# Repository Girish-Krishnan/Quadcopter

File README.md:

# Quadcopter

*Made by Girish Krishnan and Anish Kulkarni*

---

Hardware and firmware for a compact 4‑rotor UAV.
[**Watch the demo videos on YouTube!**](https://www.youtube.com/playlist?list=PLE_L-WPduPxbYMuvPQKa1v5fUpK1VIxrP)

|| |
|---|---|

This project contains hardware and firmware for a custom 4‑rotor UAV. The design is based on the ATmega128RFA1 microcontroller which integrates a 2.4 GHz radio. The repository includes the printed circuit board layout, flight controller firmware, and code for a handheld remote.

**Note**: The specific code files and CAD files are currently private, but you can contact me for more details.

## Table of Contents
- [Quadcopter](#quadcopter)
  - [Table of Contents](#table-of-contents)
  - [Features](#features)
  - [System Overview](#system-overview)
  - [Hardware Overview](#hardware-overview)
  - [Firmware Overview](#firmware-overview)
    - [Wireless Protocol](#wireless-protocol)
    - [Flight Controller](#flight-controller)
    - [Remote Firmware](#remote-firmware)
    - [PID Control Loops](#pid-control-loops)
    - [State Machines](#state-machines)
      - [Quadcopter](#quadcopter-1)
      - [Remote](#remote)
  - [Building and Uploading](#building-and-uploading)

## Features
- Flight controller based on the ATmega128RFA1 with integrated 2.4 GHz radio
- Handheld remote with dual gimbals, LCD and menu navigation
- Telemetry link for battery monitoring and state feedback
- PID tuning directly from the remote
- Four-layer PCB with on-board ESC drivers and IMU

## System Overview

The project consists of two main pieces of hardware:

1. **Quadcopter** – a compact flight controller board driving four brushless motors via electronic speed controllers (ESCs).
2. **Remote** – a handheld transmitter with gimbal sticks, buttons and an LCD that sends pilot commands over 2.4 GHz.

The diagram below summarizes the high–level flow of data and control.

```mermaid
graph LR
    Remote[(Handheld Remote)] -- 2.4GHz --> MCU[ATmega128RFA1]
    MCU --> IMU[LSM6DSOX IMU]
    MCU --> ESCs
    ESCs --> Motors
    MCU -- Telemetry --> Remote
```

## Hardware Overview

The quadcopter PCB is a four‑layer board measuring 119×119 mm with red soldermask and white silkscreen. Major components:

- **ATmega128RFA1** MCU with onboard 2.4 GHz transceiver
- **LSM6DSOX** IMU for 3‑axis gyro and accelerometer
- FET motor drivers for four brushless ESCs
- Power regulation, battery monitor (via `BAT_SENSE_PIN`), and status LEDs
- Connectors for an external receiver and programming headers

Here is a schematic overview of the quadcopter:

Here is the layout of the quadcopter PCB, showing the placement of components and routing:

Here are pictures of the top and bottom layers of the PCB:

|||
|---|---|
| Top Layer | Bottom Layer |

## Firmware Overview

### Wireless Protocol

The on-board radio communicates with the remote using packets. Packets carry user commands, PID gains, trims, and telemetry such as battery level.

### Flight Controller

The flight controller reads the LSM6DSOX IMU using the Adafruit AHRS library. A complementary filter and PID loop produce motor outputs:

- Desired roll/pitch/yaw are received from the remote.
- IMU data is converted to angles and rates.
- Proportional, integral and derivative terms are computed every loop.
- Four PWM outputs drive the motors which mixes PID outputs to each rotor.

State transitions are received wirelessly. The code also reports back battery percentage every second.

### Remote Firmware

The remote uses analog gimbals, push buttons, a rotary encoder and a SerLCD display. It calibrates the joystick range to map raw ADC values to 0–255 and stores them in EEPROM. In the armed state, pressing the encoder or buttons adjusts trim values which are sent in each packet.

Incoming packets from the quad provide its state and battery status so the remote can display feedback to the user.

The remote hardware exposes the following controls:

- Two gimbal sticks (yaw/throttle and roll/pitch) wired to analog inputs A0–A3.
- A rotary encoder with push‑button for menu navigation.
- Five directional buttons for trims and menu actions.
- A small serial LCD showing mode and battery levels.

### PID Control Loops

Here is the setup used for tuning the PID for the roll and pitch axes:

The flight controller stabilizes the aircraft using three independent PID loops
for roll, pitch and yaw. Error values are computed from the difference between
the desired setpoint (received from the remote) and the measured angle or rate
from the IMU. Each loop produces a correction that is mixed into the individual
motor commands.

```mermaid
graph TD
    R[Remote input] -->|setpoint| E[Error]
    IMU -- feedback --> E
    E --> P[P gain]
    E --> I[I gain]
    E --> D[D gain]
    P --> SUM
    I --> SUM
    D --> SUM
    SUM --> MIX(Motor Mixer)
    MIX --> Motors
```

### State Machines
#### Quadcopter

```mermaid
stateDiagram-v2
    direction LR
    [*] --> QUAD_RESET
    QUAD_RESET --> DISARMED: Startup complete
    DISARMED --> ARMED: Receive ARM
    ARMED --> DISARMED: Receive DISARM or link loss
```

#### Remote

```mermaid
stateDiagram-v2
    direction LR
    [*] --> DISARMED
    DISARMED --> CALIBRATION: Center button
    CALIBRATION --> DISARMED: Save calibration
    DISARMED --> ARMED: Stick combo 3s
    ARMED --> DISARMED: Center button or QUAD_RESET from quad
 ```

## Building and Uploading

Follow the instructions in [NVSL QuadClass Resources](https://github.com/NVSL/QuadClass-Resources/tree/master) to get started.

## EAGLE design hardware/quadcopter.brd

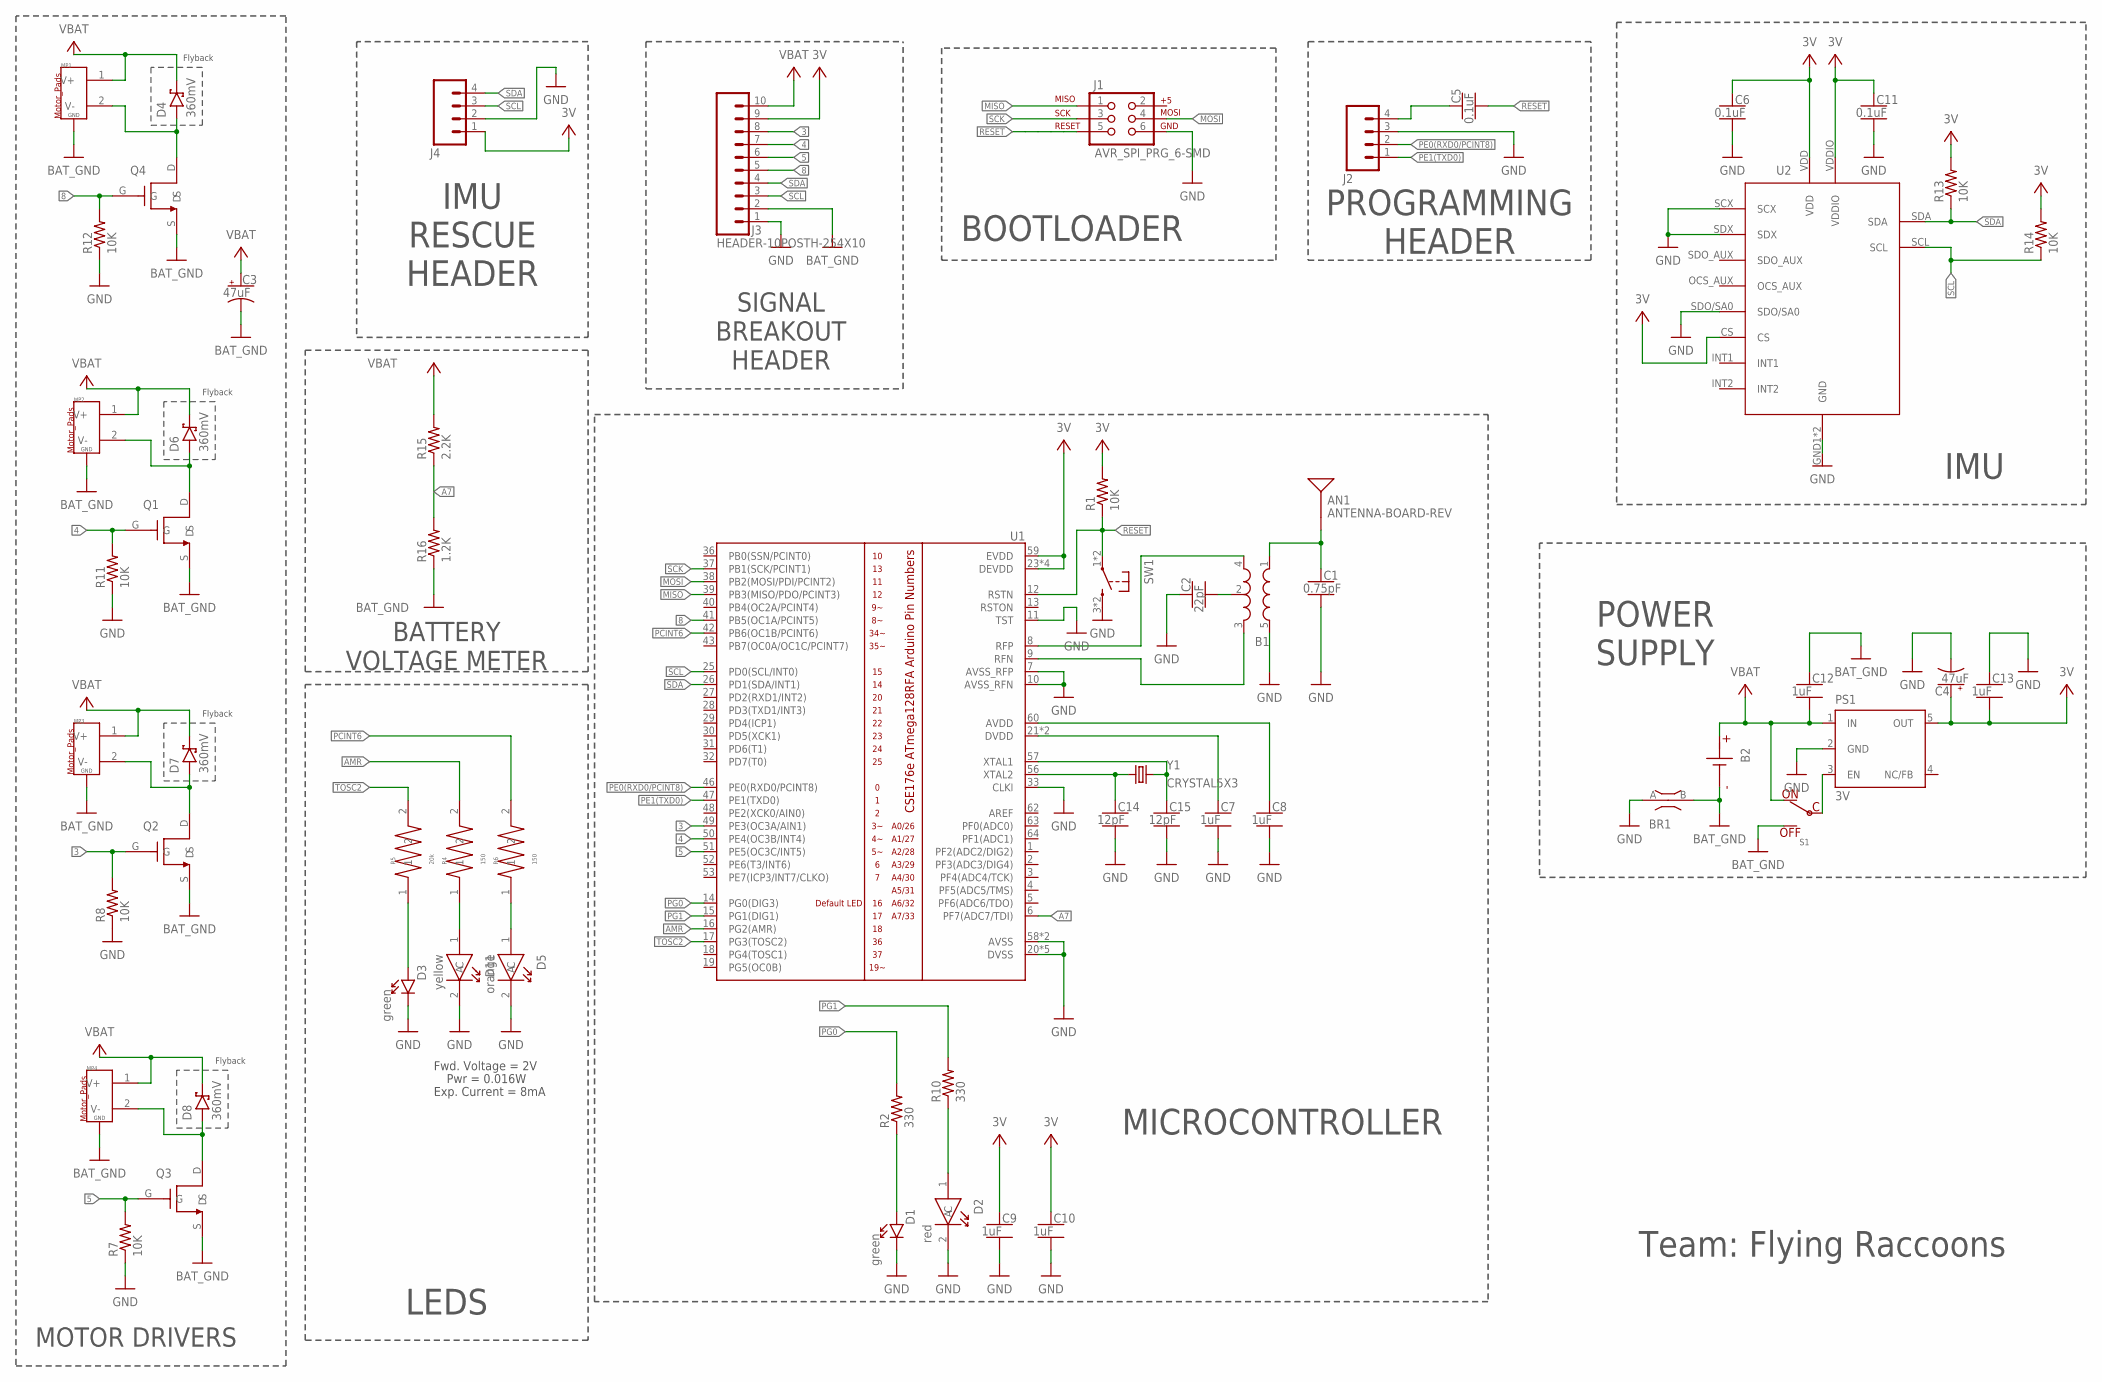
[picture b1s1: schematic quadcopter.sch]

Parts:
AN1: ANTENNA-BOARD-REV; ANT_PCB_2.4GHZ_NRF8001_1.6MM_1OZ_REV
B1: BALUN0805; BALUN
B2: BATTERY-SCREW-TERMINAL; SCREW-TERMINAL-1X2-2.54MM
BR1: NET_BRIDGE-NET-BRIDGE; BRIDGE
C1: 0.75pF; CAPC2012X140_HS
C2: 22pF; CAPC2012X140_HS
C3, C4: 47uF; CAPMP3216X180
C5, C6, C11: 0.1uF; CAPC2012X140_HS
C7, C8, C9, C10, C12, C13: 1uF; CAPC2012X140_HS
C14, C15: 12pF; CAPC2012X140_HS
D1, D3: green; LEDSC125X200X120-2_HS
D2: red; LED-LTST-C170EKT
D4, D6, D7, D8: 360mV; SODFL3516X96
D5: orange; LED-LTST-C170EKT
D11: yellow; LED-LTST-C170EKT
J1: AVR_SPI_PRG_6-SMD; 2X3-SMD
J2, J4: HEADER-4POS-0.1IN-FEMALE-SMD-BOTTOM-ENTRY; HEADER-1X4-BOTTOM-ENTRY
J3: HEADER-10POSTH-254X10; HDRV10W63P254_10X1_2540X254H838_HS
MP1, MP2, MP3, MP4: MOTOR_PADS_GND-MOLEX-SMD; MOLEX-0532610271
PS1: 3V; SOT23-DBV
Q1, Q2, Q3, Q4: NMOSFET; SOTFL95P237X112-3N
R1, R7, R8, R11, R12, R13, R14: 10K; RESC2012X60_HS
R2, R10: 330; RESC2012X60_HS
R4, R6: 150; 0805_RESISTOR
R5: 20k; 0805_RESISTOR
R15: 2.2K; RESC2012X60_HS
R16: 1.2K; RESC2012X60_HS
S1: POWER-SWITCH-MFS201N-9-Z-SMD-EDGE; JS102011SAQN
SW1: PUSHBUTTON_-4.5X4.5; 4.5MM_TACTILE_SWITCH_TL3305AF160QG
U1: ATMEGA128RFA1; QFN-64
U2: IMU_LSM6DS0XTR-IMU-LSM6DS0XTR; IMU_LSM6DS0XTR
Y1: CRYSTAL5X3; CRYSTAL-SMD-5X3

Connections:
3: J3.8, Q2.G, R8.2, U1.49 (PE3(OC3A/AIN1))
3V: C4.1 (+), C6.1, C9.1, C10.1, C11.1, C13.2, J3.9, J4.1, PS1.5 (OUT), R1.2, R13.2, R14.2, U1.23 (DEVDD), U1.34 (DEVDD), U1.44 (DEVDD), U1.54 (DEVDD), U1.59 (EVDD), U2.CS, U2.VDD, U2.VDDIO
4: J3.7, Q1.G, R11.2, U1.50 (PE4(OC3B/INT4))
5: J3.6, Q3.G, R7.2, U1.51 (PE5(OC3C/INT5))
8: J3.5, Q4.G, R12.2, U1.41 (PB5(OC1A/PCINT5))
A7: R15.1, R16.2, U1.6 (PF7(ADC7/TDI))
AMR: R4.2, U1.16 (PG2(AMR))
BAT_GND: B2.1 (N), BR1.B, C3.2 (-), C12.1, J3.2, MP1.G1 (GND), MP1.G2 (GND), MP2.G1 (GND), MP2.G2 (GND), MP3.G1 (GND), MP3.G2 (GND), MP4.G1 (GND), MP4.G2 (GND), Q1.S, Q2.S, Q3.S, Q4.S, R16.1, S1.A (OFF)
GND: B1.5 (GND), BR1.A, C1.2, C2.1, C4.2 (-), C6.2, C7.2, C8.2, C9.2, C10.2, C11.2, C13.1, C14.2, C15.2, D1.C, D2.2 (C), D3.C, D5.2 (C), D11.2 (C), J1.6, J2.3, J3.1, J4.2, PS1.2 (GND), R7.1, R8.1, R11.1, R12.1, SW1.3 (2), SW1.4 (2), U1.7 (AVSS_RFP), U1.10 (AVSS_RFN), U1.11 (TST), U1.20 (DVSS), U1.24 (DVSS), U1.33 (CLKI), U1.35 (DVSS), U1.45 (DVSS), U1.55 (DVSS), U1.58 (AVSS), U1.61 (AVSS), U2.GND1 (GND), U2.GND2 (GND), U2.SCX, U2.SDO/SA0, U2.SDX
MISO: J1.1, U1.39 (PB3(MISO/PDO/PCINT3))
MOSI: J1.4, U1.38 (PB2(MOSI/PDI/PCINT2))
unnamed: B1.4 (OUT1), U1.8 (RFP)
unnamed: C15.1, U1.57 (XTAL1), Y1.3 (2)
unnamed: C14.1, U1.56 (XTAL2), Y1.1
unnamed: C7.1, U1.21 (DVDD), U1.22 (DVDD)
unnamed: C8.1, U1.60 (AVDD)
unnamed: B1.3 (OUT2), U1.9 (RFN)
unnamed: B1.2 (GND), C2.2
unnamed: AN1.FEED, B1.1 (IN), C1.1
unnamed: D1.A, R2.1
unnamed: D2.1 (A), R10.1
unnamed: PS1.3 (EN), S1.C
unnamed: D3.A, R5.1
unnamed: D11.1 (A), R4.1
unnamed: D5.1 (A), R6.1
unnamed: C5.1, J2.4
unnamed: D6.2 (A), MP2.2 (V-), Q1.D
unnamed: D7.2 (A), MP3.2 (V-), Q2.D
unnamed: D8.2 (A), MP4.2 (V-), Q3.D
unnamed: D4.2 (A), MP1.2 (V-), Q4.D
PCINT6: R6.2, U1.42 (PB6(OC1B/PCINT6))
PE0(RXD0/PCINT8): J2.2, U1.46 (PE0(RXD0/PCINT8))
PE1(TXD0): J2.1, U1.47 (PE1(TXD0))
PG0: R2.2, U1.14 (PG0(DIG3))
PG1: R10.2, U1.15 (PG1(DIG1))
RESET: C5.2, J1.5, R1.1, SW1.1, SW1.2 (1), U1.12 (RSTN)
SCK: J1.3, U1.37 (PB1(SCK/PCINT1))
SCL: J3.3, J4.3, R14.1, U1.25 (PD0(SCL/INT0)), U2.SCL
SDA: J3.4, J4.4, R13.1, U1.26 (PD1(SDA/INT1)), U2.SDA
TOSC2: R5.2, U1.17 (PG3(TOSC2))
VBAT: B2.2, C3.1 (+), C12.2, D4.1 (C), D6.1 (C), D7.1 (C), D8.1 (C), J3.10, MP1.1 (V+), MP2.1 (V+), MP3.1 (V+), MP4.1 (V+), PS1.1 (IN), R15.2, S1.B (ON)

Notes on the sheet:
IMU
BOOTLOADER
Flyback
MOTOR DRIVERS
SIGNAL BREAKOUT HEADER
IMU RESCUE HEADER
MICROCONTROLLER
POWER SUPPLY
PROGRAMMING HEADER
LEDS
BATTERY VOLTAGE METER
Team: Flying Raccoons
Fwd. Voltage = 2V
Pwr = 0.016W
Exp. Current = 8mA

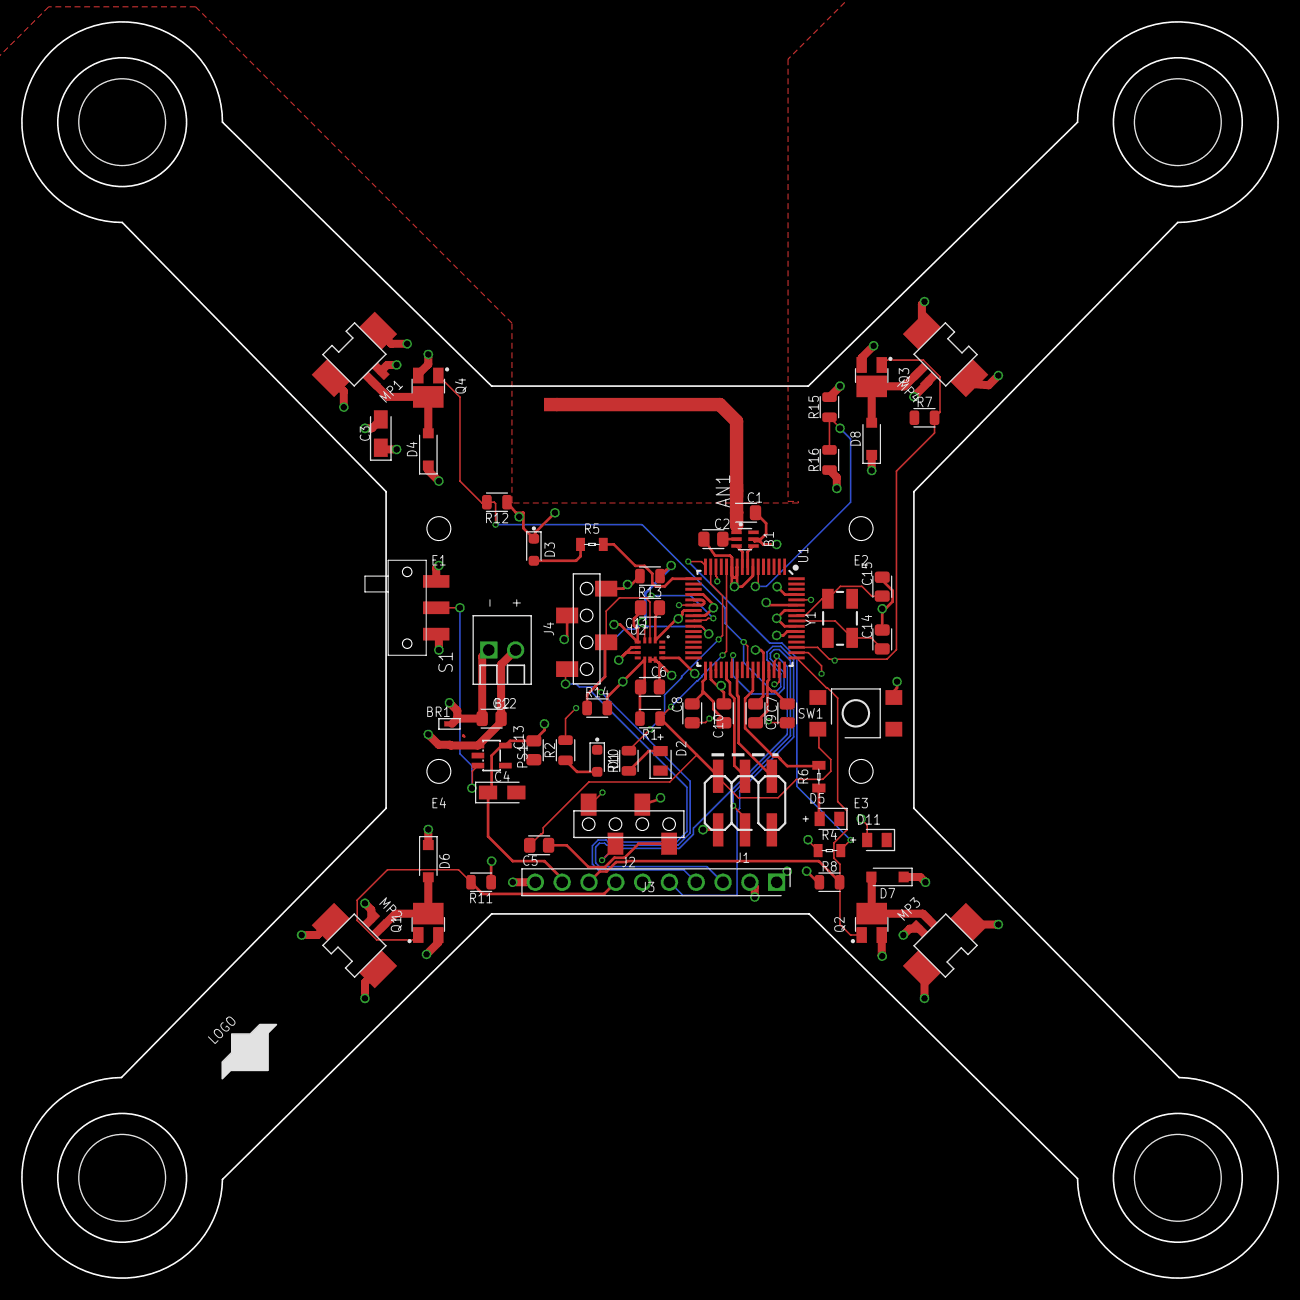
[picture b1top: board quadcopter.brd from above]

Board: 4 copper layers, 119.0 x 119.0 mm, 70 parts (0 on the bottom side), 41 nets.

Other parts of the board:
E1, E2, E3, E4: 2-56-MOUNTING-HOLE-NO-METAL
E$1: LAYER_LABELS
LOGO: DECORATIONS
P1, P2, P3, P4: MOTOR_AND_PROP

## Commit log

2025-07-09 All code files
2025-07-09 Expand project README
2025-07-10 docs: expand README with diagrams
2025-07-28 Add comprehensive deep dive document
2025-08-27 docs: add state machine diagrams
2025-08-27 docs: adjust state machine diagrams
